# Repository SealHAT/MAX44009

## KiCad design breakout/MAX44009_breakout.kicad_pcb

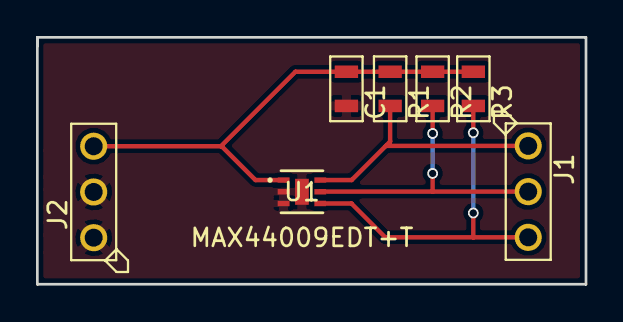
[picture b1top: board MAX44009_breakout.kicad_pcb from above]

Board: 2 copper layers, 30.5 x 13.7 mm, 7 parts (0 on the bottom side), 5 nets.

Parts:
C1: 1uF; MF_Passives-C0805
J1, J2: CON_01X03_PTH_2.54MM; MF_Connectors-PTH_2.54MM_01X03
R1, R2, R3: 10k; MF_Passives-R0805
U1: MAX44009EDT+T; MAX44009EDT&plus_T

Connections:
+3V3: C1.1, J2.3, R1.1, R2.1, R3.1, U1.1
GNDREF: C1.2, J2.1, J2.2, U1.2, U1.3, U1.7
unnamed: J1.1, R1.2, U1.6
unnamed: J1.2, R2.2, U1.5
unnamed: J1.3, R3.2, U1.4

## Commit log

2018-01-22 added breakout folder and ignores
2018-01-23 Light Breakout Layout
2018-02-15 started typed header
2018-02-15 removed kicad design
2018-02-15 Added function outlies and stubs for read and write i2c functions
2018-02-19 added new project file and added hardware IO to lib
2018-02-20 finished example project. working as is
2018-02-20 removed arduino file
2018-02-20 added doxygen configuration and ignore file bits
2018-02-20 changed library to use i2c_m_sysc structs instead of io_read/write, which cleaned up most read functions.
2018-02-20 transformed read_integer_lux to an inline function that calls read nested inside integer conversion
2018-02-20 changed git attributes so that all source files will always have LF endings
2018-02-21 reordered functions in header to compile correctly
2018-02-21 changed driver to async and started changing library
2018-02-21 started changing lib
2018-02-24 fixed typo in types and also renamed to create namespace
2018-02-24 added new un-broken files
2018-02-24 re-added max44009 main file
2018-02-24 added max44009 source files
2018-02-24 added Wall and fixed a few warnings
2018-03-15 updated USB lib
2018-03-15 updated main for usb lib
2018-05-20 better error returns and inlined read and write functions
2018-05-20 got rid of math inlcude for pow()
2018-05-26 removed bool and atmel start depend
2018-06-10 moved public defines to seperate header to play nice with GUI
2018-06-12 fixed bug by clearing return variable
